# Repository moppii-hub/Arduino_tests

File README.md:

# Arduino_tests
Some TEST project using Arduino to build musical instruments.  

# Contents
- 00_helloworld (using 2NanoMusic board)
The basics for using switches, leds, sounds.  

- 01_I2C (using 2NanoMusic board)
Easy samples about using I2C connection.  

- 02_MIDI (using 2NanoMusic board)
Easy examples about using MIDI communication.  

- 03_ISR (using 2NanoMusic board)
Easy examples about using AVR timer-interrupt functions.  

- 04_PWM (using 2NanoMusic board and an additional speaker on D11 pin)
Using AVR timer-interrupt and PWM output in order to play multi-channel sounds.  

- 05_MIDI_ISR (using 2NanoMusic board and an additional speaker on D11 pin)
The example of recieve MIDI, play tone(multi), and send MIDI using AVR interrupt in order to DSP and timing-control.  

- 06_LED_ISR (using 2NanoMusic board)
Using AVR timer-interrupt to control LED and SW matrix, and to control MIDI-send sequencialy.  

# Hardware
Schematics, parts, and PWB designs all are in kicad directory.  
Using two Arduino nano boards, one speaker, some LEDs and 6x6 tactile switches.

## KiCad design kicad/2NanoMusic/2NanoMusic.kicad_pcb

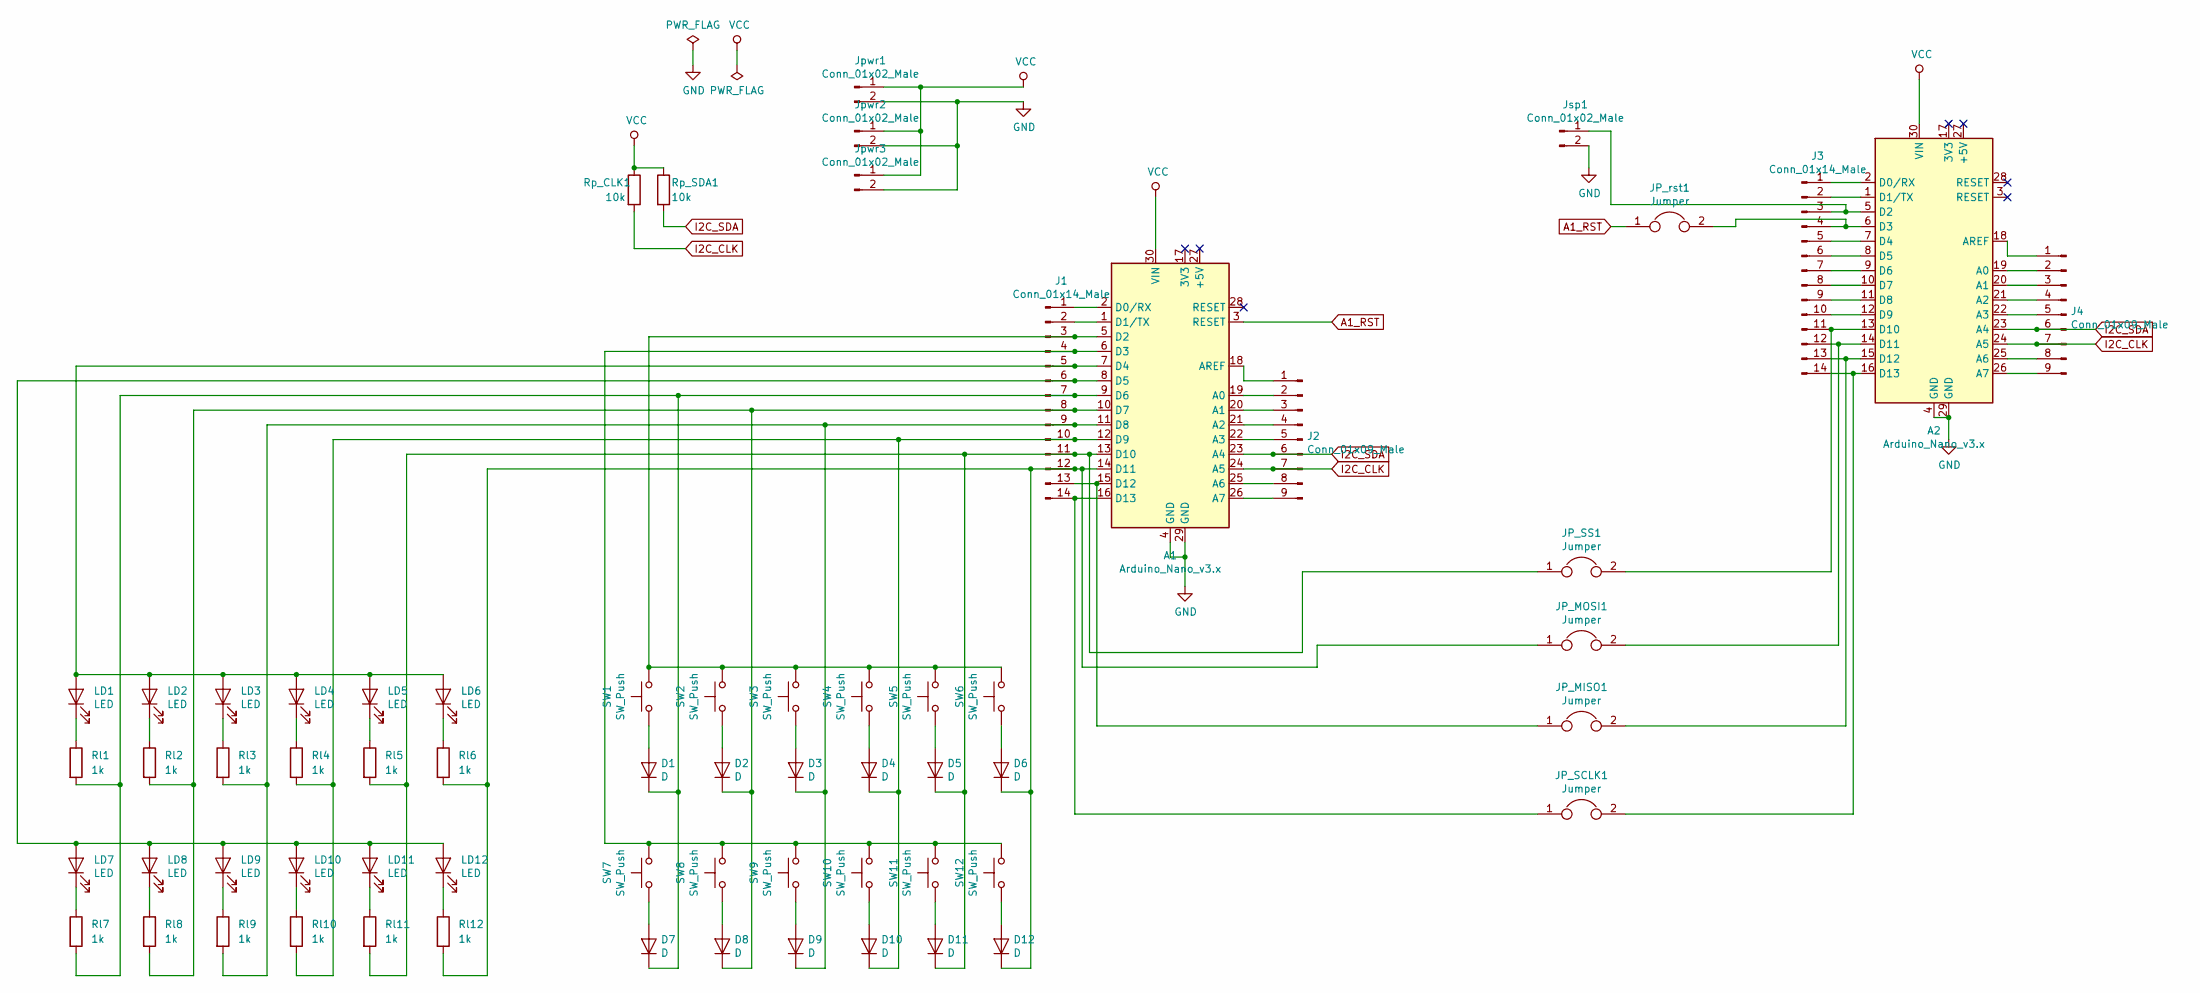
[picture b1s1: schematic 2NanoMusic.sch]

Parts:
A1, A2: Arduino_Nano_v3.x; Arduino_Nano
D1, D2, D3, D4, D5, D6, D7, D8, D9, D10, D11, D12: D; D_5W_P5.08mm_Vertical_AnodeUp
J1, J3: Conn_01x14_Male; PinHeader_1x14_P2.54mm_Vertical
J2, J4: Conn_01x09_Male; PinHeader_1x09_P2.54mm_Vertical
JP_MISO1: Jumper; SolderJumper-2_P1.3mm_Open_RoundedPad1.0x1.5mm
JP_MOSI1: Jumper; SolderJumper-2_P1.3mm_Open_RoundedPad1.0x1.5mm
JP_SCLK1: Jumper; SolderJumper-2_P1.3mm_Open_RoundedPad1.0x1.5mm
JP_SS1: Jumper; SolderJumper-2_P1.3mm_Open_RoundedPad1.0x1.5mm
JP_rst1: Jumper; SolderJumper-2_P1.3mm_Open_RoundedPad1.0x1.5mm
Jpwr1, Jpwr2, Jpwr3: Conn_01x02_Male; PinHeader_1x02_P2.54mm_Vertical
Jsp1: Conn_01x02_Male; PinHeader_1x02_P2.54mm_Vertical
LD1, LD2, LD3, LD4, LD5, LD6, LD7, LD8, LD9, LD10, LD11, LD12: LED; LED_D5.0mm
Rl1, Rl2, Rl3, Rl4, Rl5, Rl6, Rl7, Rl8, Rl9, Rl10, Rl11, Rl12: 1k; R_Axial_DIN0207_L6.3mm_D2.5mm_P5.08mm_Vertical
Rp_CLK1: 10k; R_Axial_DIN0207_L6.3mm_D2.5mm_P5.08mm_Vertical
Rp_SDA1: 10k; R_Axial_DIN0207_L6.3mm_D2.5mm_P5.08mm_Vertical
SW1, SW2, SW3, SW4, SW5, SW6, SW7, SW8, SW9, SW10, SW11, SW12: SW_Push; SW_PUSH_6mm

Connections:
A1_RST: A1.3 (RESET), JP_rst1.1
GND: A1.4 (GND), A1.29 (GND), A2.4 (GND), A2.29 (GND), Jpwr1.2, Jpwr2.2, Jpwr3.2, Jsp1.2
I2C_CLK: A1.24 (A5), A2.24 (A5), J2.7, J4.7, Rp_CLK1.2
I2C_SDA: A1.23 (A4), A2.23 (A4), J2.6, J4.6, Rp_SDA1.2
unnamed: A1.1 (D1/TX), J1.2
unnamed: A1.2 (D0/RX), J1.1
unnamed: A1.5 (D2), J1.3, SW1.2, SW2.2, SW3.2, SW4.2, SW5.2, SW6.2
unnamed: A1.6 (D3), J1.4, SW7.2, SW8.2, SW9.2, SW10.2, SW11.2, SW12.2
unnamed: A1.7 (D4), J1.5, LD1.2 (A), LD2.2 (A), LD3.2 (A), LD4.2 (A), LD5.2 (A), LD6.2 (A)
unnamed: A1.8 (D5), J1.6, LD7.2 (A), LD8.2 (A), LD9.2 (A), LD10.2 (A), LD11.2 (A), LD12.2 (A)
unnamed: A1.9 (D6), D1.1 (K), D7.1 (K), J1.7, Rl1.2, Rl7.2
unnamed: A1.10 (D7), D2.1 (K), D8.1 (K), J1.8, Rl2.2, Rl8.2
unnamed: A1.11 (D8), D3.1 (K), D9.1 (K), J1.9, Rl3.2, Rl9.2
unnamed: A1.12 (D9), D4.1 (K), D10.1 (K), J1.10, Rl4.2, Rl10.2
unnamed: A1.13 (D10), D5.1 (K), D11.1 (K), J1.11, JP_SS1.1, Rl5.2, Rl11.2
unnamed: A1.14 (D11), D6.1 (K), D12.1 (K), J1.12, JP_MOSI1.1, Rl6.2, Rl12.2
unnamed: A1.15 (D12), J1.13, JP_MISO1.1
unnamed: A1.16 (D13), J1.14, JP_SCLK1.1
unnamed: A1.18 (AREF), J2.1
unnamed: A1.19 (A0), J2.2
unnamed: A1.20 (A1), J2.3
unnamed: A1.21 (A2), J2.4
unnamed: A1.22 (A3), J2.5
unnamed: A1.25 (A6), J2.8
unnamed: A1.26 (A7), J2.9
unnamed: A2.1 (D1/TX), J3.2
unnamed: A2.2 (D0/RX), J3.1
unnamed: A2.5 (D2), J3.3, Jsp1.1
unnamed: A2.6 (D3), J3.4, JP_rst1.2
unnamed: A2.7 (D4), J3.5
unnamed: A2.8 (D5), J3.6
unnamed: A2.9 (D6), J3.7
unnamed: A2.10 (D7), J3.8
unnamed: A2.11 (D8), J3.9
unnamed: A2.12 (D9), J3.10
unnamed: A2.13 (D10), J3.11, JP_SS1.2
unnamed: A2.14 (D11), J3.12, JP_MOSI1.2
unnamed: A2.15 (D12), J3.13, JP_MISO1.2
unnamed: A2.16 (D13), J3.14, JP_SCLK1.2
unnamed: A2.18 (AREF), J4.1
unnamed: A2.19 (A0), J4.2
unnamed: A2.20 (A1), J4.3
unnamed: A2.21 (A2), J4.4
unnamed: A2.22 (A3), J4.5
unnamed: A2.25 (A6), J4.8
unnamed: A2.26 (A7), J4.9
unnamed: D1.2 (A), SW1.1
unnamed: D2.2 (A), SW2.1
unnamed: D3.2 (A), SW3.1
unnamed: D4.2 (A), SW4.1
unnamed: D5.2 (A), SW5.1
unnamed: D6.2 (A), SW6.1
unnamed: D7.2 (A), SW7.1
unnamed: D8.2 (A), SW8.1
unnamed: D9.2 (A), SW9.1
unnamed: D10.2 (A), SW10.1
unnamed: D11.2 (A), SW11.1
unnamed: D12.2 (A), SW12.1
unnamed: LD1.1 (K), Rl1.1
unnamed: LD2.1 (K), Rl2.1
unnamed: LD3.1 (K), Rl3.1
unnamed: LD4.1 (K), Rl4.1
unnamed: LD5.1 (K), Rl5.1
unnamed: LD6.1 (K), Rl6.1
unnamed: LD7.1 (K), Rl7.1
unnamed: LD8.1 (K), Rl8.1
unnamed: LD9.1 (K), Rl9.1
unnamed: LD10.1 (K), Rl10.1
unnamed: LD11.1 (K), Rl11.1
unnamed: LD12.1 (K), Rl12.1
VCC: A1.30 (VIN), A2.30 (VIN), Jpwr1.1, Jpwr2.1, Jpwr3.1, Rp_CLK1.1, Rp_SDA1.1

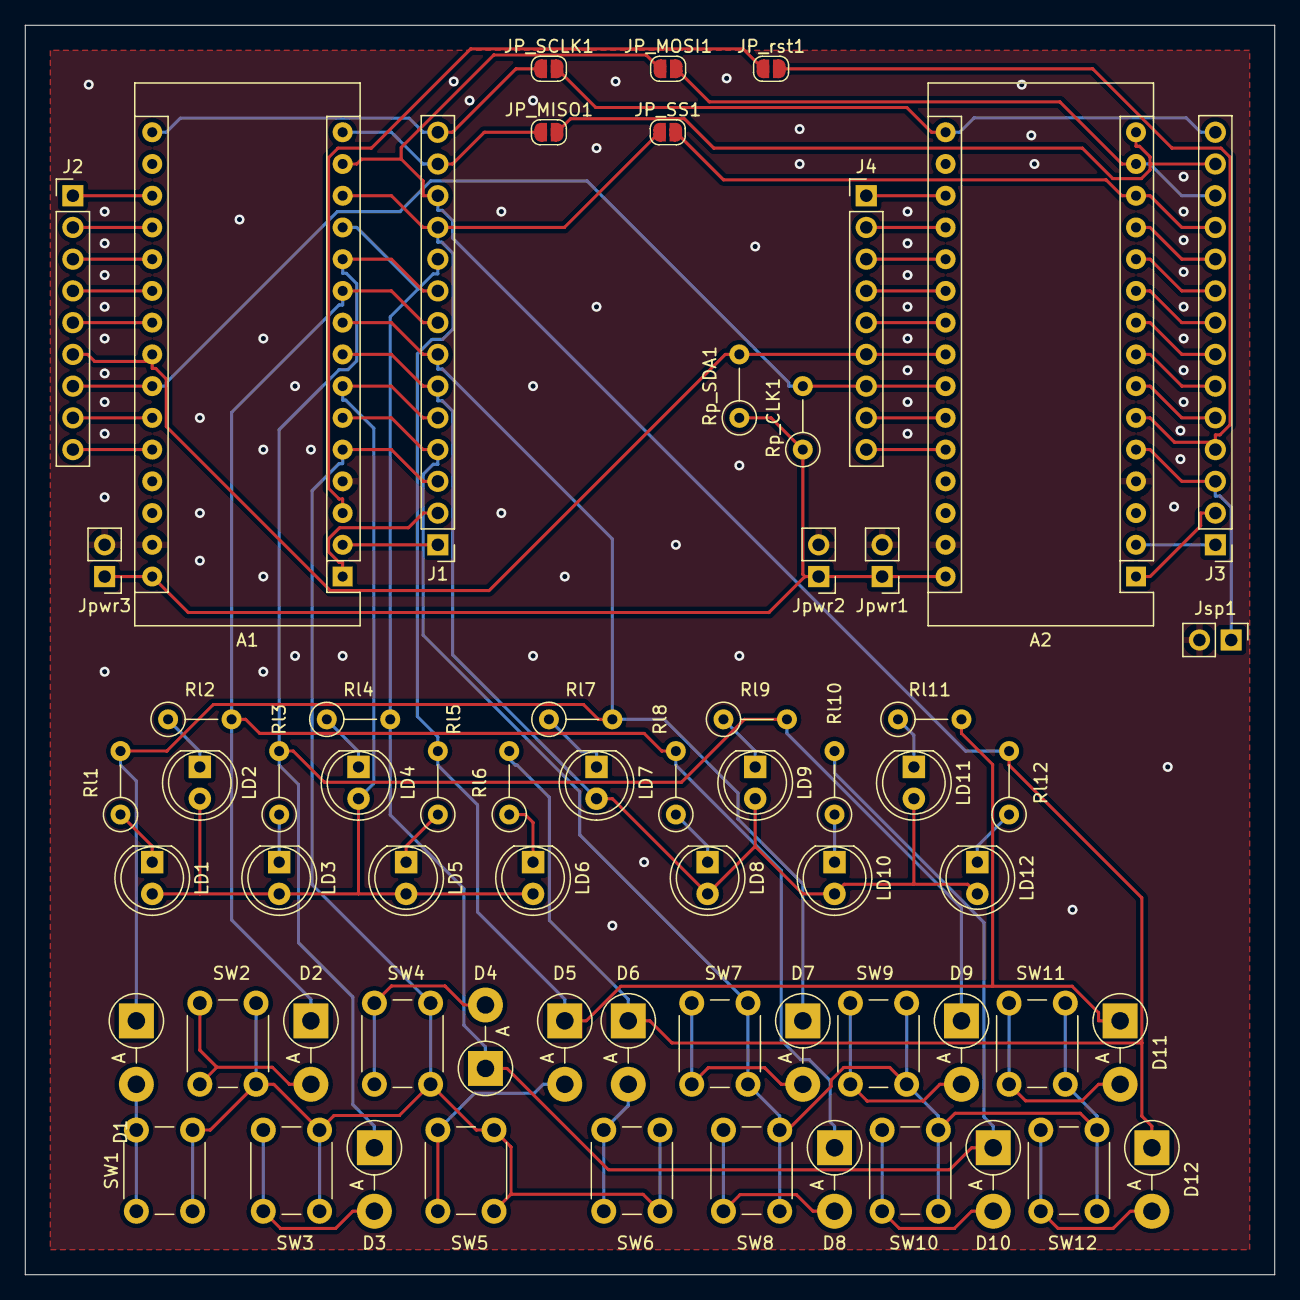
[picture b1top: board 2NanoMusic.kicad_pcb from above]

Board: 2 copper layers, 100.0 x 100.0 mm, 65 parts (0 on the bottom side), 71 nets.

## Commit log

2020-06-26 1st commit
2020-06-26 change README.md
2020-06-27 add ISR examples
2020-06-27 add PWM functions
2020-06-27 add MIDI ISR examples
2020-07-11 add 06_LED_ISR
